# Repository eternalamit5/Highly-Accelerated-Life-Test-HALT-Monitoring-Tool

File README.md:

# Highly Accelerated Life Test (HALT) Profile Monitoring Tool

1. Highly Accelerated Life Testing (HALT) Profile is stress screening methodology where real profiles of data is used to evaluate the reliability of electronics devices, mainly Printed Circuit Boards (PCBs).

2. This project aims at building a tool capable of monitoring HALT Program for identifying defects and weak links in the PCBs.

## Components Used

1. Espressif ESP32 Microcontroller

2. Bosch BMI 160 Inertial Measurement Unit

## Problem
- Lack of proper test screening leads to premature failure of electronics product.

Fig: Capacitor breakage observed during vibration HALT program

- Comparison of raw and calibrated Accelerometer data when Z-axis is facing upward

- Comparison of raw and calibrated Gyroscope data

## Calibration Methodology:

- Three-point calibration of Accelerometer X-axis

- Regression analysis for Gyroscope X-axis data when angular speed= 120 Degree/Sec

## Snapshot of Sensor Dashboard

## Note

1. Since the IoT Stack is very often used in IoT Setups, therefore it is independent, dockerized and can be used standalone for various scenarios. The IoT stack is present in the directory: Highly-Accelerated-Life-Test-HALT-Monitoring-Tool/webClient/IoT Stack

2. Refer to `README.md` in each case directory for additional information.

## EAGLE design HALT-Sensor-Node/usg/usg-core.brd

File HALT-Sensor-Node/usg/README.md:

# Universal Sensor Gateway

## ESP-WROOM-32D Pin Configuration

GPIO | PIN | Functionality | Description | Comment
--|--|--|--|--
0 || Boot Button | General IO |  
1 || UART TX0    | FTDI UART | 
2 || HS2_DATA0   | quad SPI | 
3 || UART RX0    | FTDI UART | 
4 || HS2_DATA1   | quad SPI | 
5 || CS SD Card  | SPI Chip Select | OPTIONAL
6 || FLASH SCK   | Internal Flash ESP32 | 
7 || FLASH DO    | Internal Flash ESP32 | 
8 || FLASH D1    | Internal Flash ESP32 | 
9 || FLASH D2    | Internal Flash ESP32 | U1RXD via Jumper
10 || FLASH D3   | Internal Flash ESP32 | U1TXD via Jumper
11 |  | FLASH CMD | Internal Flash ESP32
12 |  | HS2_DATA2 / TDI | quad SPI | ALSO: JTAG segger
13 |  | HS2_DATA3 / TCK | quad SPI | ALSO: JTAG segger
14 |  | HS2_CLK / TMS | quad SPI | ALSO: JTAG segger
15 |  | HS2_CMD / TDO | quad SPI | ALSO: JTAG segger
16 |  | UART RX2 | CELL UART |
17 |  | UART TX2 | CELL UART |
18 |  | VSPI SCK | mikroBUS SPI |
19 |  | VSPI MISO / Q | mikroBUS SPI |
20 |  |  |  | N/A
21 |  | CS mikroBUS | SPI Chip Select | OPTIONAL
22 |  | Ext.IO | General IO | OPTIONAL
23 |  | VSPI MOSI / D | mikroBUS SPI |
24 |  |  |  | N/A
25 |  | SARA-R4 PWR | General IO |
26 |  | SARA-R4 RESET | General IO |
27 |  | User LED | General IO | OPTIONAL
28 |  |  |  | N/A
29 |  |  |  | N/A
30 |  |  |  | N/A
31 |  |  |  | N/A
32 |  | I2C SCL | Sensor I2C |
33 |  | I2C SDA | Sensor I2C |
34 |  | Ext.Input | General INPUT | OPTIONAL
35 |  |  | General INPUT |
36 |  |  | General INPUT |
37 |  |  |  | N/A
38 |  |  |  | N/A
39 |  |  | General INPUT |
40 |  |  |  | N/A

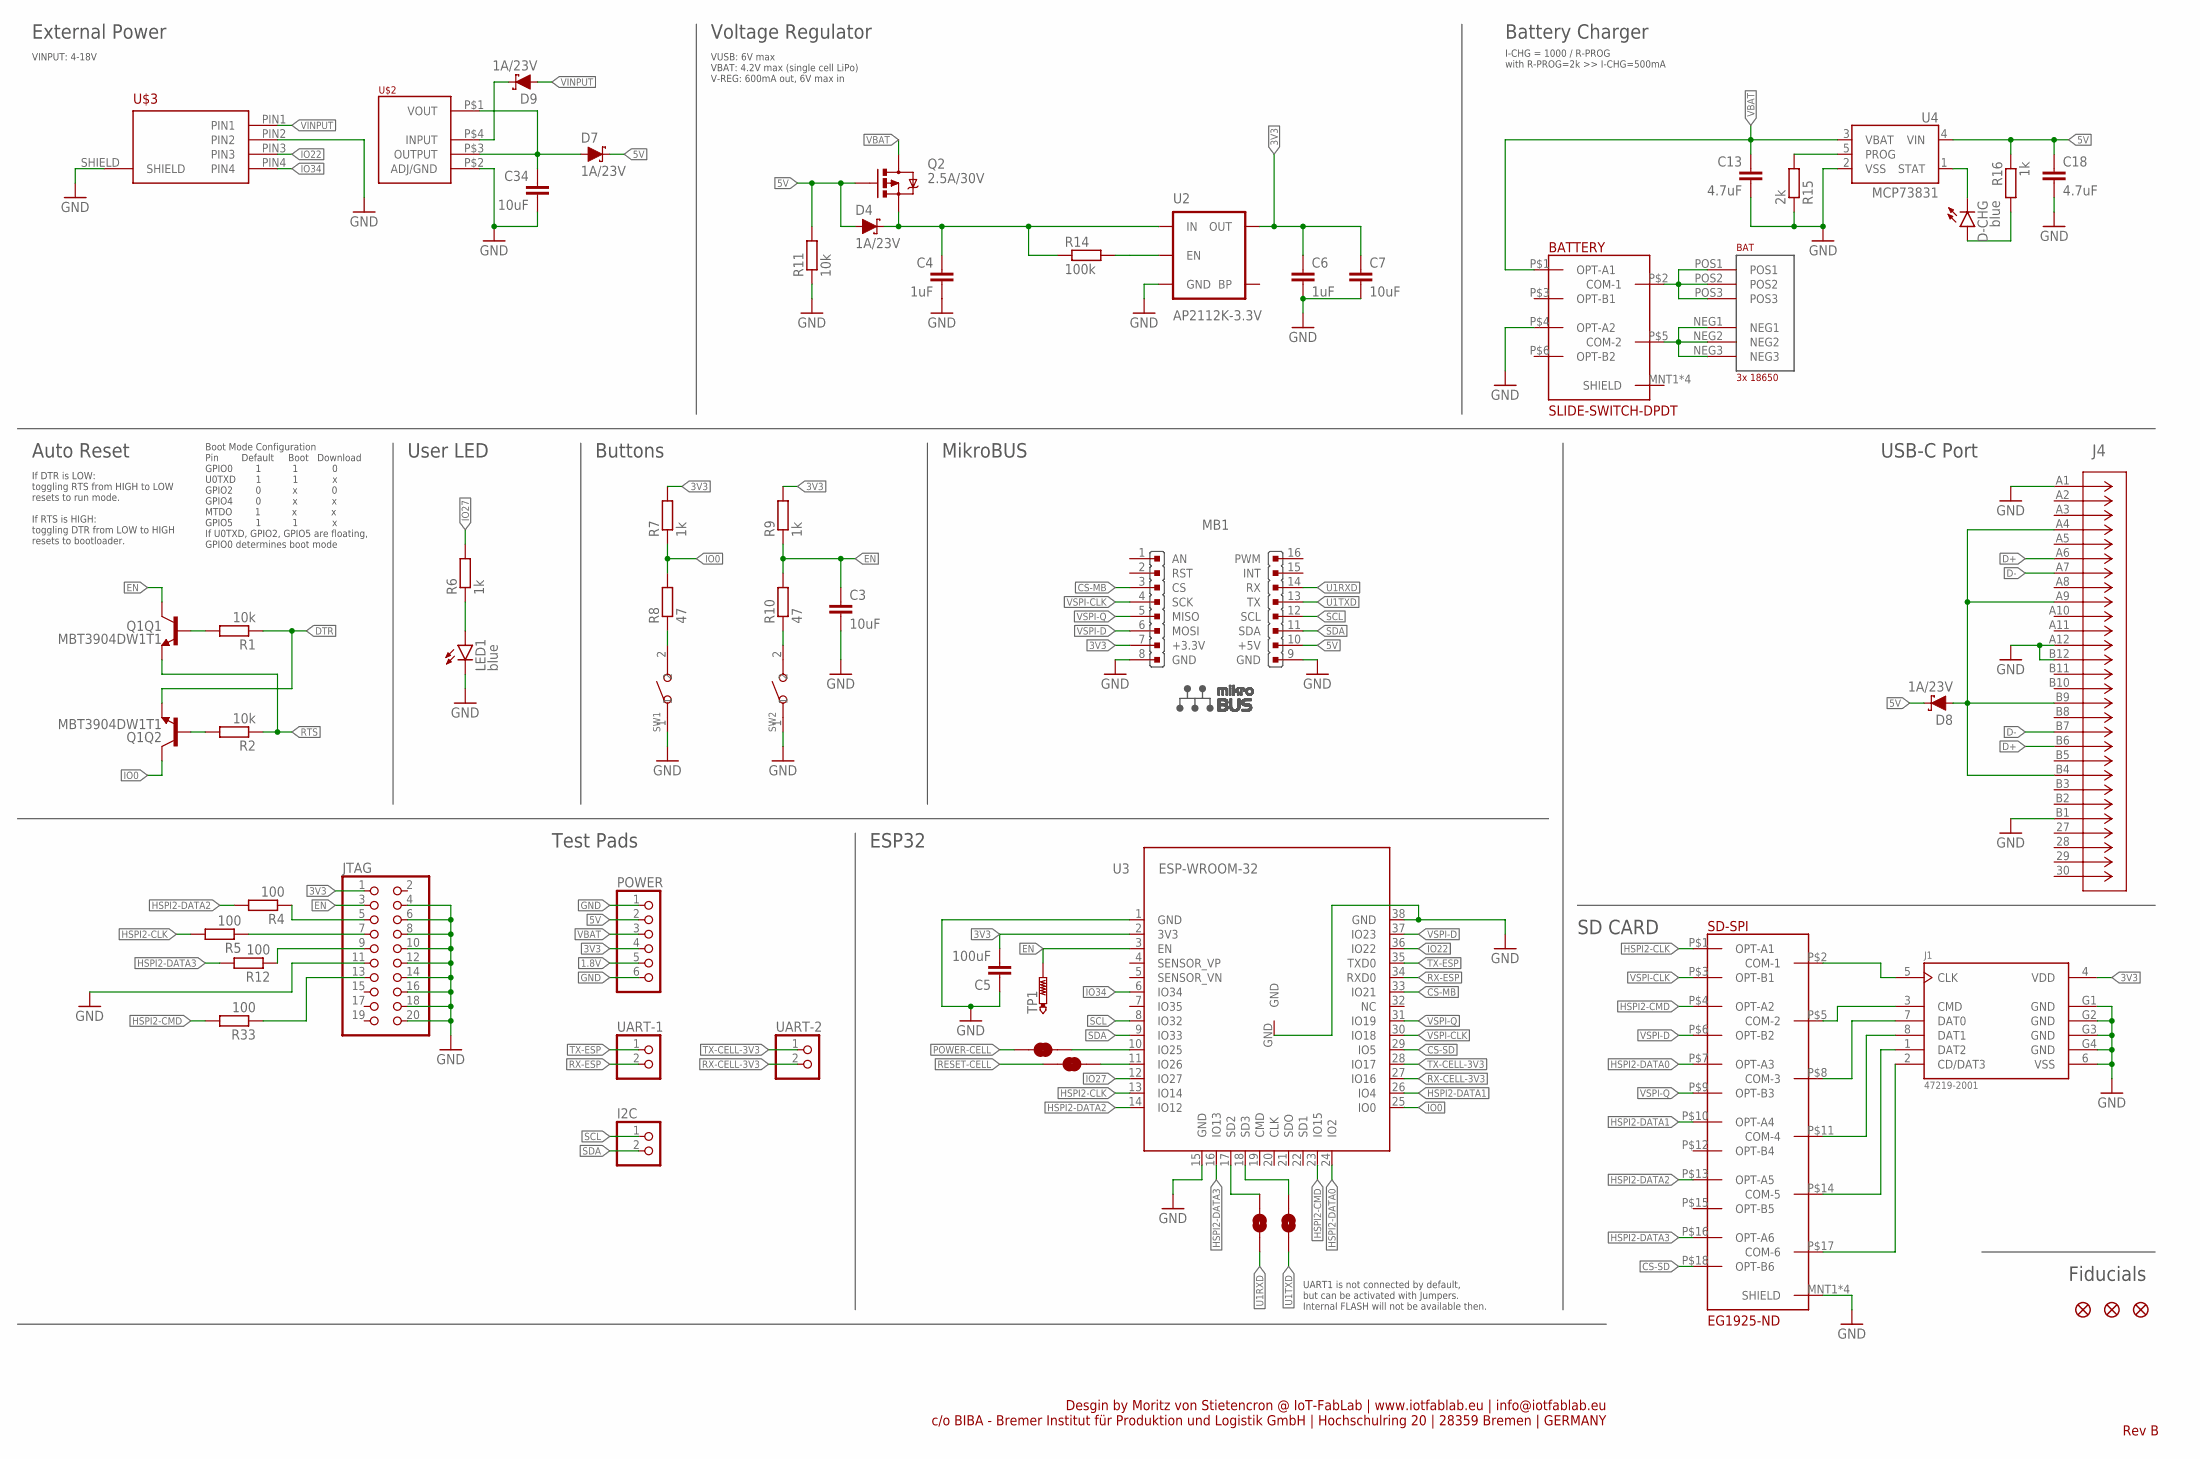
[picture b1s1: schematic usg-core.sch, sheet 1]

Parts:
BAT: 3x 18650; BK-18650-PC6
BATTERY: SLIDE-SWITCH-DPDT
C3, C7, C34: 10uF; C0603
C4, C6: 1uF; C0603
C5: 100uF; C1206
C13, C18: 4.7uF; C0603
D4, D7, D8, D9: 1A/23V; SOD-323
D-CHG: blue; CHIP-LED0603
FD1, FD2, FD3: FIDUCIAL1X2; FIDUCIAL-1X2
I2C: PINHD-1X2; 1X02
J1: 47219-2001; MOLEX_47219-2001
J4: DX07S024WJ3R400; CONN_DX07S024WJ3R400
JP10, JP11: JUMPER-SMT_2_NC_TRACE_SILK; SMT-JUMPER_2_NC_TRACE_SILK
JTAG: PINHD-2X10; 2X10
LED1: blue; CHIP-LED0603
MB1: MIKROBUS
POWER: PINHD-1X6; 1X06
Q1: MBT3904DW1T1; SC70-6
Q2: 2.5A/30V; SOT23-3@1
R1, R2, R11: 10k; R0603
R4, R5, R12, R33: 100; R0603
R6, R7, R9, R16: 1k; R0603
R8, R10: 47; R0603
R14: 100k; R0603
R15: 2k; R0603
SD-SPI: EG1925-ND; SLIDE-SWITCH-6PDT
SJ1, SJ2: JUMPER-SMT_2_NO_SILK; SMT-JUMPER_2_NO_SILK
SW1, SW2: SMD-BUTTON(2P-3.0X2.5X1.2+0.4MM)-B3U-1000P-2P-SMD; SW2-2.6-3.0X2.5X1.2+0.4MM
TP1: PTR1B1,27; B1,27
U2: AP2112K-3.3V; SOT23-5
U3: ESP-WROOM-32
U4: MCP73831; SOT23-5
U$2: LDO-AZ1117I; SOT223
U$3: SACC-CI-M12FSD-4CON-L90
UART-1, UART-2: PINHD-1X2; 1X02

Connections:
1.8V: POWER.5; also elsewhere on the board
3V3: C5.2, C6.1, C7.1, J1.4 (VDD), JTAG.1, MB1.7 (+3.3V), POWER.4, R7.2, R9.2, U2.5 (OUT), U3.2 (3V3); also elsewhere on the board
5V: C18.1, D4.A, D7.C, D8.C, MB1.10 (+5V), POWER.2, Q2.1 (G), R11.2, R16.1, U4.4 (VIN); also elsewhere on the board
BTN1: R10.1, SW2.2
CHG: D-CHG.C, U4.1 (STAT)
CS-MB: MB1.3 (CS), U3.33 (IO21)
CS-SD: SD-SPI.P$18 (OPT-B6), U3.29 (IO5)
D+: J4.A6, J4.B6; also elsewhere on the board
D-: J4.A7, J4.B7; also elsewhere on the board
DTR: Q1.1 (E), R1.1; also elsewhere on the board
EN: C3.1, JTAG.3, Q1.3 (C), R9.1, R10.2, TP1.TP, U3.3 (EN)
EN1: R14.2, U2.3 (EN)
GND: BATTERY.P$4 (OPT-A2), C3.2, C4.2, C5.1, C6.2, C7.2, C13.2, C18.2, C34.2, J1.6 (VSS), J1.G1 (GND), J1.G2 (GND), J1.G3 (GND), J1.G4 (GND), J4.A1, J4.A12, J4.B1, J4.B12, JTAG.4, JTAG.6, JTAG.8, JTAG.10, JTAG.11, JTAG.12, JTAG.14, JTAG.16, JTAG.18, JTAG.20, LED1.C, MB1.8 (GND), MB1.9 (GND), POWER.1, POWER.6, R11.1, R15.1, SD-SPI.MNT1 (SHIELD), SD-SPI.MNT2 (SHIELD), SD-SPI.MNT3 (SHIELD), SD-SPI.MNT4 (SHIELD), SW1.1, SW2.1, U2.2 (GND), U3.1 (GND), U3.15 (GND), U3.38 (GND), U3.GND, U4.2 (VSS), U$2.P$2 (ADJ/GND), U$3.PIN2, U$3.SHIELD; also elsewhere on the board
HSPI2-CLK: R5.2, SD-SPI.P$1 (OPT-A1), U3.13 (IO14)
HSPI2-CMD: R33.2, SD-SPI.P$4 (OPT-A2), U3.23 (IO15)
HSPI2-DATA0: SD-SPI.P$7 (OPT-A3), U3.24 (IO2)
HSPI2-DATA1: SD-SPI.P$10 (OPT-A4), U3.26 (IO4)
HSPI2-DATA2: R4.2, SD-SPI.P$13 (OPT-A5), U3.14 (IO12)
HSPI2-DATA3: R12.2, SD-SPI.P$16 (OPT-A6), U3.16 (IO13)
IO0: Q1.6 (C), R7.1, R8.2, U3.25 (IO0)
IO22: U3.36 (IO22), U$3.PIN3
IO27: R6.2, U3.12 (IO27)
IO34: U3.6 (IO34), U$3.PIN4
unnamed: D9.C, U$2.P$4 (INPUT)
unnamed: D-CHG.A, R16.2
unnamed: R15.2, U4.5 (PROG)
unnamed: Q1.5 (B), R1.2
unnamed: LED1.A, R6.1
unnamed: R8.1, SW1.2
unnamed: Q1.2 (B), R2.2
unnamed: D8.A, J4.A4, J4.A9, J4.B4, J4.B9
unnamed: JP10.2, U3.10 (IO25)
unnamed: JP11.2, U3.11 (IO26)
unnamed: SJ1.2, U3.17 (SD2)
unnamed: SJ2.2, U3.18 (SD3)
unnamed: J1.5 (CLK), SD-SPI.P$2 (COM-1)
unnamed: J1.3 (CMD), SD-SPI.P$5 (COM-2)
unnamed: J1.2 (CD/DAT3), SD-SPI.P$17 (COM-6)
unnamed: J1.1 (DAT2), SD-SPI.P$14 (COM-5)
unnamed: J1.8 (DAT1), SD-SPI.P$11 (COM-4)
unnamed: J1.7 (DAT0), SD-SPI.P$8 (COM-3)
unnamed: JTAG.5, R4.1
unnamed: JTAG.7, R5.1
unnamed: JTAG.9, R12.1
unnamed: JTAG.13, R33.1
unnamed: BAT.POS1, BAT.POS2, BAT.POS3, BATTERY.P$2 (COM-1)
unnamed: BAT.NEG1, BAT.NEG2, BAT.NEG3, BATTERY.P$5 (COM-2)
POWER-CELL: JP10.1; also elsewhere on the board
RESET-CELL: JP11.1; also elsewhere on the board
RTS: Q1.4 (E), R2.1; also elsewhere on the board
RX-CELL-3V3: U3.27 (IO16), UART-2.2; also elsewhere on the board
RX-ESP: U3.34 (RXD0), UART-1.2; also elsewhere on the board
SCL: I2C.1, MB1.12 (SCL), U3.8 (IO32); also elsewhere on the board
SDA: I2C.2, MB1.11 (SDA), U3.9 (IO33); also elsewhere on the board
TX-CELL-3V3: U3.28 (IO17), UART-2.1; also elsewhere on the board
TX-ESP: U3.35 (TXD0), UART-1.1; also elsewhere on the board
U1RXD: MB1.14 (RX), SJ1.1
U1TXD: MB1.13 (TX), SJ2.1
VBAT: BATTERY.P$1 (OPT-A1), C13.1, POWER.3, Q2.3 (D), U4.3 (VBAT)
VIN: C4.1, D4.C, Q2.2 (S), R14.1, U2.1 (IN)
VINPUT: D9.A, U$3.PIN1
VOUT: C34.1, D7.A, U$2.P$1 (VOUT), U$2.P$3 (OUTPUT)
VSPI-CLK: MB1.4 (SCK), SD-SPI.P$3 (OPT-B1), U3.30 (IO18)
VSPI-D: MB1.6 (MOSI), SD-SPI.P$6 (OPT-B2), U3.37 (IO23)
VSPI-Q: MB1.5 (MISO), SD-SPI.P$9 (OPT-B3), U3.31 (IO19)

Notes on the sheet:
Voltage Regulator
Battery Charger
Auto Reset
User LED
USB-C Port
ESP32
Buttons
Fiducials
Desgin by Moritz von Stietencron @ IoT-FabLab | www.iotfablab.eu | info@iotfablab.eu c/o BIBA - Bremer Institut für Produktion und Logistik GmbH | Hochschulring 20 | 28359 Bremen | GERMANY
Rev B
Test Pads
I-CHG = 1000 / R-PROG with R-PROG=2k >> I-CHG=500mA
VUSB: 6V max VBAT: 4.2V max (single cell LiPo) V-REG: 600mA out, 6V max in
If DTR is LOW: toggling RTS from HIGH to LOW resets to run mode. If RTS is HIGH: toggling DTR from LOW to HIGH resets to bootloader.
Boot Mode Configuration Pin Default Boot Download GPIO0 1 1 0 U0TXD 1 1 x GPIO2 0 x 0 GPIO4 0 x x MTDO 1 x x GPIO5 1 1 x If U0TXD, GPIO2, GPIO5 are floating, GPIO0 determines boot mode
MikroBUS
SD CARD
UART1 is not connected by default, but can be activated with Jumpers. Internal FLASH will not be available then.
External Power
VINPUT: 4-18V

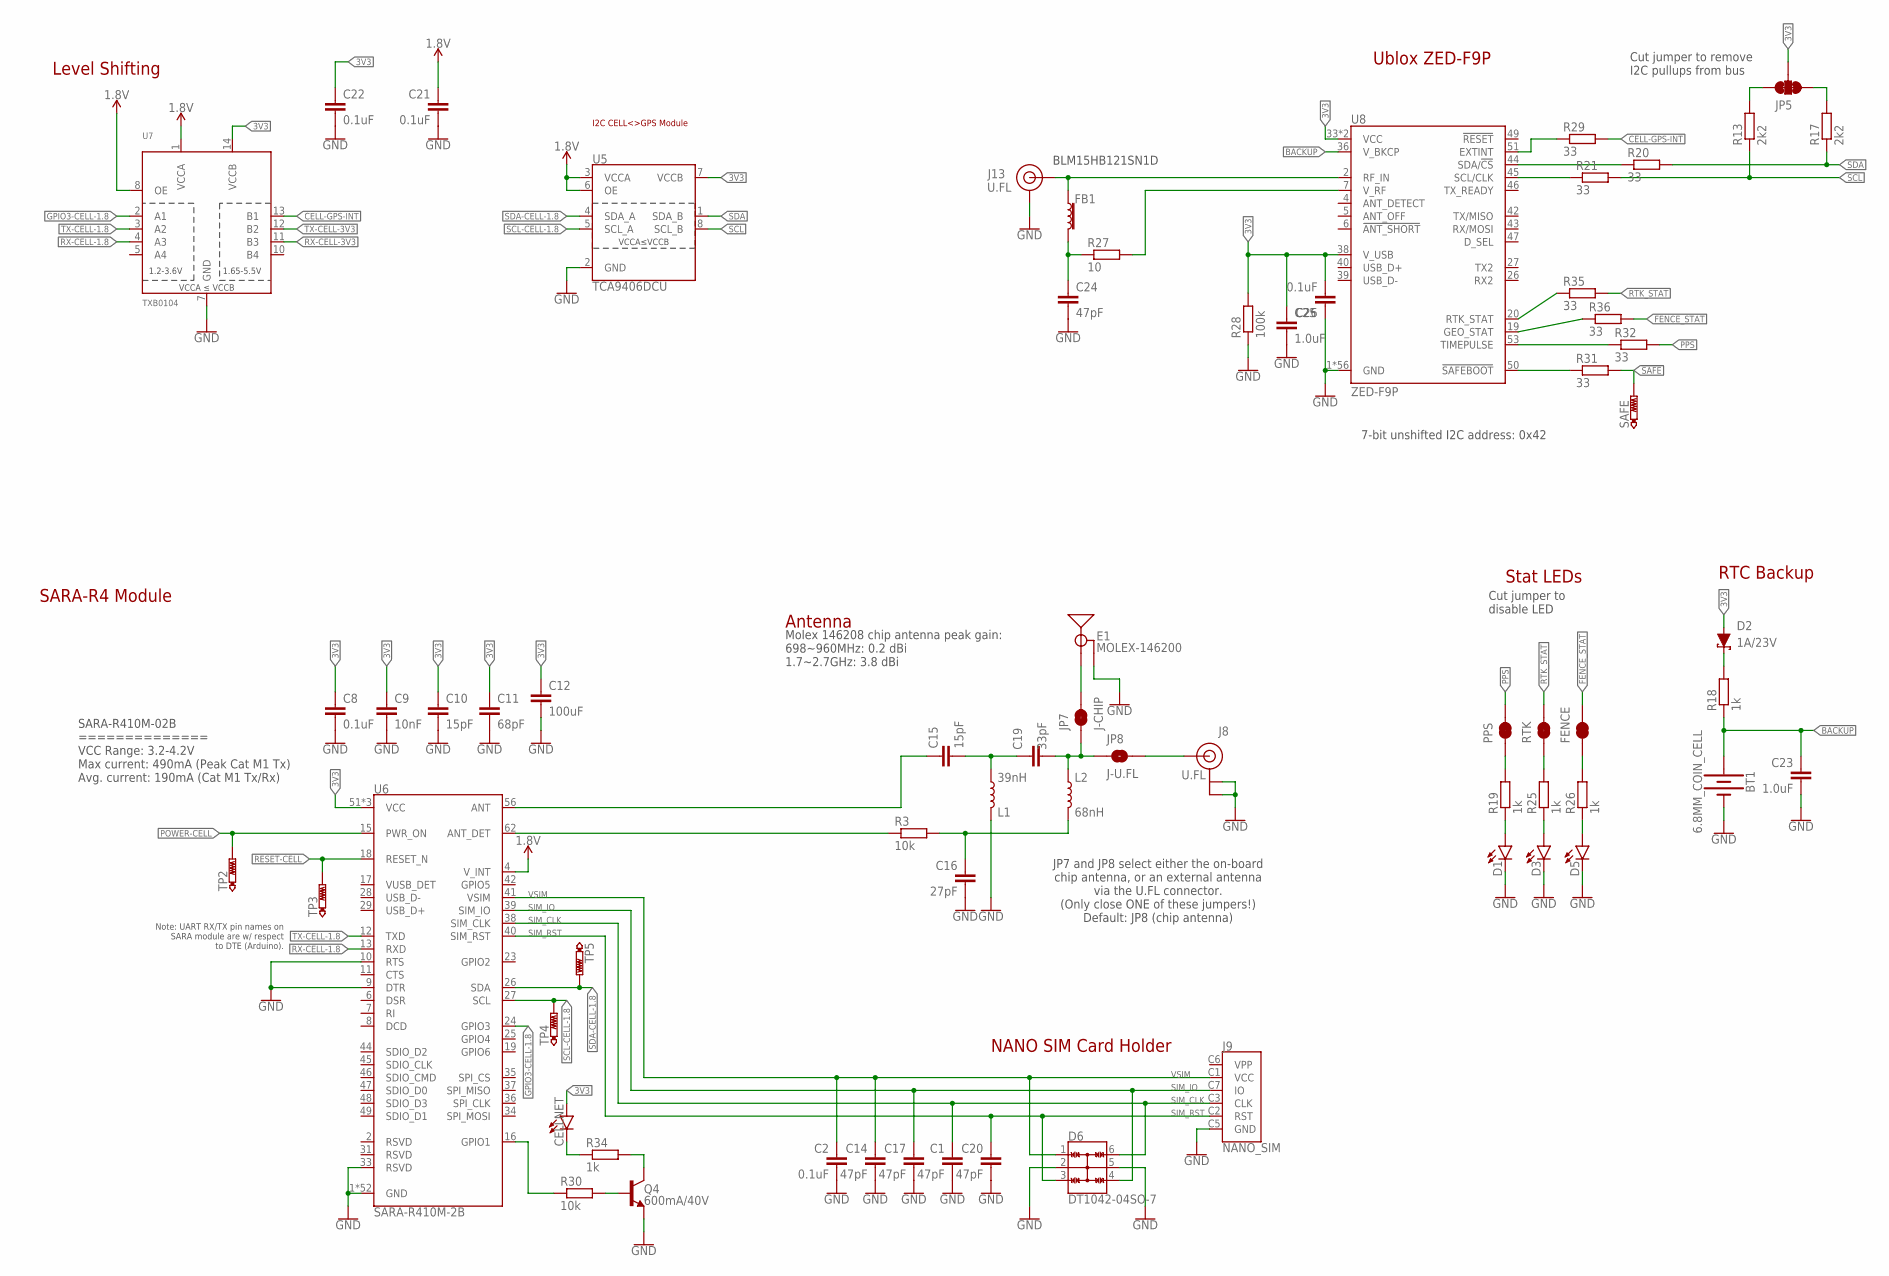
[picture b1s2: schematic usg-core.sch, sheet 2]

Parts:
BT1: 6.8MM_COIN_CELL; BATTCON-6.8MM
C1, C14, C17, C20, C24: 47pF; C0603
C2, C8, C21, C22, C26: 0.1uF; C0603
C9: 10nF; C0603
C10, C15: 15pF; C0603
C11: 68pF; C0603
C12: 100uF; C1206
C16: 27pF; C0603
C19: 33pF; C0603
C23, C25: 1.0uF; C0603
CELLNET: blue; CHIP-LED0603
D1, D3, D5: blue; CHIP-LED0603
D2: 1A/23V; SOD-323
D6: DT1042-04SO-7; SOT23-6L
E1: MOLEX-146200; MOLEX_146200
FB1: FERRITE_BEAD-120_OHM-0402; 0402
FENCE: JUMPER-SMT_2_NC_TRACE_SILK; SMT-JUMPER_2_NC_TRACE_SILK
J8, J13: U.FL
J9: NANO_SIM; NANO_SIM_WURTH_693043020611
JP5: JUMPER-SMT_3_2-NC_TRACE_SILK; SMT-JUMPER_3_2-NC_TRACE_SILK
JP7: J-CHIP; SMT-JUMPER_2_NC_TRACE_NO-SILK
JP8: J-U.FL; SMT-JUMPER_2_NO_NO-SILK
L1: 39nH; 0603
L2: 68nH; 0603
PPS: JUMPER-SMT_2_NC_TRACE_SILK; SMT-JUMPER_2_NC_TRACE_SILK
Q4: 600mA/40V; SOT23-3
R3, R30: 10k; R0603
R13, R17: 2k2; R0603
R18, R19, R25, R26, R34: 1k; R0603
R20, R21, R29, R31, R32, R35, R36: 33; R0603
R27: 10; R0603
R28: 100k; R0603
RTK: JUMPER-SMT_2_NC_TRACE_SILK; SMT-JUMPER_2_NC_TRACE_SILK
SAFE: PTR1B1,27; B1,27
TP2, TP3, TP4, TP5: PTR1B1,27; B1,27
U5: TCA9406DCU; VSSOP-8
U6: SARA-R410M-2B; SARA-LGA
U7: TXB0104; TSSOP14
U8: ZED-F9P

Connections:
1.8V: C21.1, U5.3 (VCCA), U5.6 (OE), U6.4 (V_INT), U7.1 (VCCA), U7.8 (OE); also elsewhere on the board
3V3: C8.1, C9.1, C10.1, C11.1, C12.1, C22.1, C25.1, C26.2, CELLNET.A, D2.A, JP5.2, R28.2, U5.7 (VCCB), U6.51 (VCC), U6.52 (VCC), U6.53 (VCC), U7.14 (VCCB), U8.33 (VCC), U8.34 (VCC), U8.38 (V_USB); also elsewhere on the board
!SAFE: R31.2, SAFE.TP
ANT: C15.1, U6.56 (ANT)
ANT_DET: R3.1, U6.62 (ANT_DET)
ANT_VCC: C24.1, FB1.2, R27.1
BACKUP: BT1.+, C23.1, R18.1, U8.36 (V_BKCP)
CELL-GPS-INT: R29.2, U7.13 (B1)
FENCE_STAT: FENCE.2, R36.2
GND: BT1.-, C1.2, C2.2, C8.2, C9.2, C10.2, C11.2, C12.2, C14.2, C16.2, C17.2, C20.2, C21.2, C22.2, C23.2, C24.2, C25.2, C26.1, D1.C, D3.C, D5.C, D6.2, D6.5, E1.GND, J8.1 (GND), J8.2 (GND), J9.C5 (GND), J13.1 (GND), J13.2 (GND), L1.1, Q4.2 (E), R28.1, U5.2 (GND), U6.1 (GND), U6.3 (GND), U6.5 (GND), U6.9 (DTR), U6.10 (RTS), U6.14 (GND), U6.20 (GND), U6.21 (GND), U6.22 (GND), U6.30 (GND), U6.32 (GND), U6.33 (RSVD), U6.43 (GND), U6.50 (GND), U6.54 (GND), U6.55 (GND), U6.57 (GND), U6.58 (GND), U6.59 (GND), U6.60 (GND), U6.61 (GND), U6.63 (GND), U6.64 (GND), U6.65 (GND), U6.66 (GND), U6.67 (GND), U6.68 (GND), U6.69 (GND), U6.70 (GND), U6.71 (GND), U6.72 (GND), U6.73 (GND), U6.74 (GND), U6.75 (GND), U6.76 (GND), U6.77 (GND), U6.78 (GND), U6.79 (GND), U6.80 (GND), U6.81 (GND), U6.82 (GND), U6.83 (GND), U6.84 (GND), U6.85 (GND), U6.86 (GND), U6.87 (GND), U6.88 (GND), U6.89 (GND), U6.90 (GND), U6.91 (GND), U6.92 (GND), U6.93 (GND), U6.94 (GND), U6.95 (GND), U6.96 (GND), U7.7 (GND), U8.1 (GND), U8.3 (GND), U8.12 (GND), U8.14 (GND), U8.32 (GND), U8.37 (GND), U8.41 (GND), U8.48 (GND), U8.55 (GND), U8.56 (GND), U8.57 (GND), U8.58 (GND), U8.59 (GND), U8.60 (GND), U8.61 (GND), U8.62 (GND), U8.63 (GND), U8.64 (GND), U8.65 (GND), U8.66 (GND), U8.67 (GND), U8.68 (GND), U8.69 (GND), U8.70 (GND), U8.71 (GND), U8.72 (GND), U8.73 (GND), U8.74 (GND), U8.75 (GND), U8.76 (GND), U8.77 (GND), U8.78 (GND), U8.79 (GND), U8.80 (GND), U8.81 (GND), U8.82 (GND), U8.83 (GND), U8.84 (GND), U8.85 (GND), U8.86 (GND), U8.87 (GND), U8.88 (GND), U8.89 (GND), U8.90 (GND), U8.91 (GND), U8.92 (GND), U8.93 (GND), U8.94 (GND), U8.95 (GND), U8.96 (GND), U8.97 (GND), U8.98 (GND), U8.99 (GND), U8.100 (GND), U8.101 (GND), U8.102 (GND); also elsewhere on the board
GPIO3-CELL-1.8: U6.24 (GPIO3), U7.2 (A1)
GPS_ANT1: FB1.1, J13.FEED (SIGNAL), U8.2 (RF_IN)
unnamed: C16.1, L2.2, R3.2
unnamed: C19.2, JP7.1, JP8.1, L2.1
unnamed: C15.2, C19.1, L1.2
unnamed: J8.FEED (SIGNAL), JP8.2
unnamed: E1.FEED (SIGNAL), JP7.2
unnamed: JP5.1, R17.2
unnamed: JP5.3, R13.2
unnamed: D1.A, R19.1
unnamed: PPS.1, R19.2
unnamed: D2.C, R18.2
unnamed: D3.A, R25.1
unnamed: R25.2, RTK.1
unnamed: D5.A, R26.1
unnamed: FENCE.1, R26.2
unnamed: R27.2, U8.7 (V_RF)
unnamed: R32.1, U8.53 (TIMEPULSE)
unnamed: R31.1, U8.50 (!SAFEBOOT!)
unnamed: R35.1, U8.20 (RTK_STAT)
unnamed: R36.1, U8.19 (GEO_STAT)
unnamed: R29.1, U8.51 (EXTINT)
unnamed: Q4.3 (C), R34.2
unnamed: Q4.1 (B), R30.2
unnamed: R30.1, U6.16 (GPIO1)
unnamed: CELLNET.C, R34.1
POWER-CELL: TP2.TP, U6.15 (PWR_ON); also elsewhere on the board
PPS: PPS.2, R32.2
RESET-CELL: TP3.TP, U6.18 (RESET_N); also elsewhere on the board
RTK_STAT: R35.2, RTK.2
RX-CELL-1.8: U6.13 (RXD), U7.4 (A3)
RX-CELL-3V3: U7.11 (B3); also elsewhere on the board
SCL: R13.1, R21.2, U5.8 (SCL_B); also elsewhere on the board
SCL-CELL-1.8: TP4.TP, U5.5 (SCL_A), U6.27 (SCL)
SCL_LV: R21.1, U8.45 (SCL/CLK)
SDA: R17.1, R20.2, U5.1 (SDA_B); also elsewhere on the board
SDA-CELL-1.8: TP5.TP, U5.4 (SDA_A), U6.26 (SDA)
SDA_LV: R20.1, U8.44 (SDA/!CS!)
SIM_CLK: C1.1, D6.6, J9.C3 (CLK), U6.38 (SIM_CLK)
SIM_IO: C17.1, D6.4, J9.C7 (IO), U6.39 (SIM_IO)
SIM_RST: C20.1, D6.3, J9.C2 (RST), U6.40 (SIM_RST)
TX-CELL-1.8: U6.12 (TXD), U7.3 (A2)
TX-CELL-3V3: U7.12 (B2); also elsewhere on the board
VSIM: C2.1, C14.1, D6.1, J9.C1 (VCC), U6.41 (VSIM)

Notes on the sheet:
Antenna
SARA-R4 Module
NANO SIM Card Holder
JP7 and JP8 select either the on-board chip antenna, or an external antenna via the U.FL connector. (Only close ONE of these jumpers!) Default: JP8 (chip antenna)
Note: UART RX/TX pin names on SARA module are w/ respect to DTE (Arduino).
Molex 146208 chip antenna peak gain: 698~960MHz: 0.2 dBi 1.7~2.7GHz: 3.8 dBi
SARA-R410M-02B ============== VCC Range: 3.2-4.2V Max current: 490mA (Peak Cat M1 Tx) Avg. current: 190mA (Cat M1 Tx/Rx)
Level Shifting
I2C CELL<>GPS Module
7-bit unshifted I2C address: 0x42
Ublox ZED-F9P
Cut jumper to remove I2C pullups from bus
BLM15HB121SN1D
RTC Backup
Stat LEDs
Cut jumper to disable LED

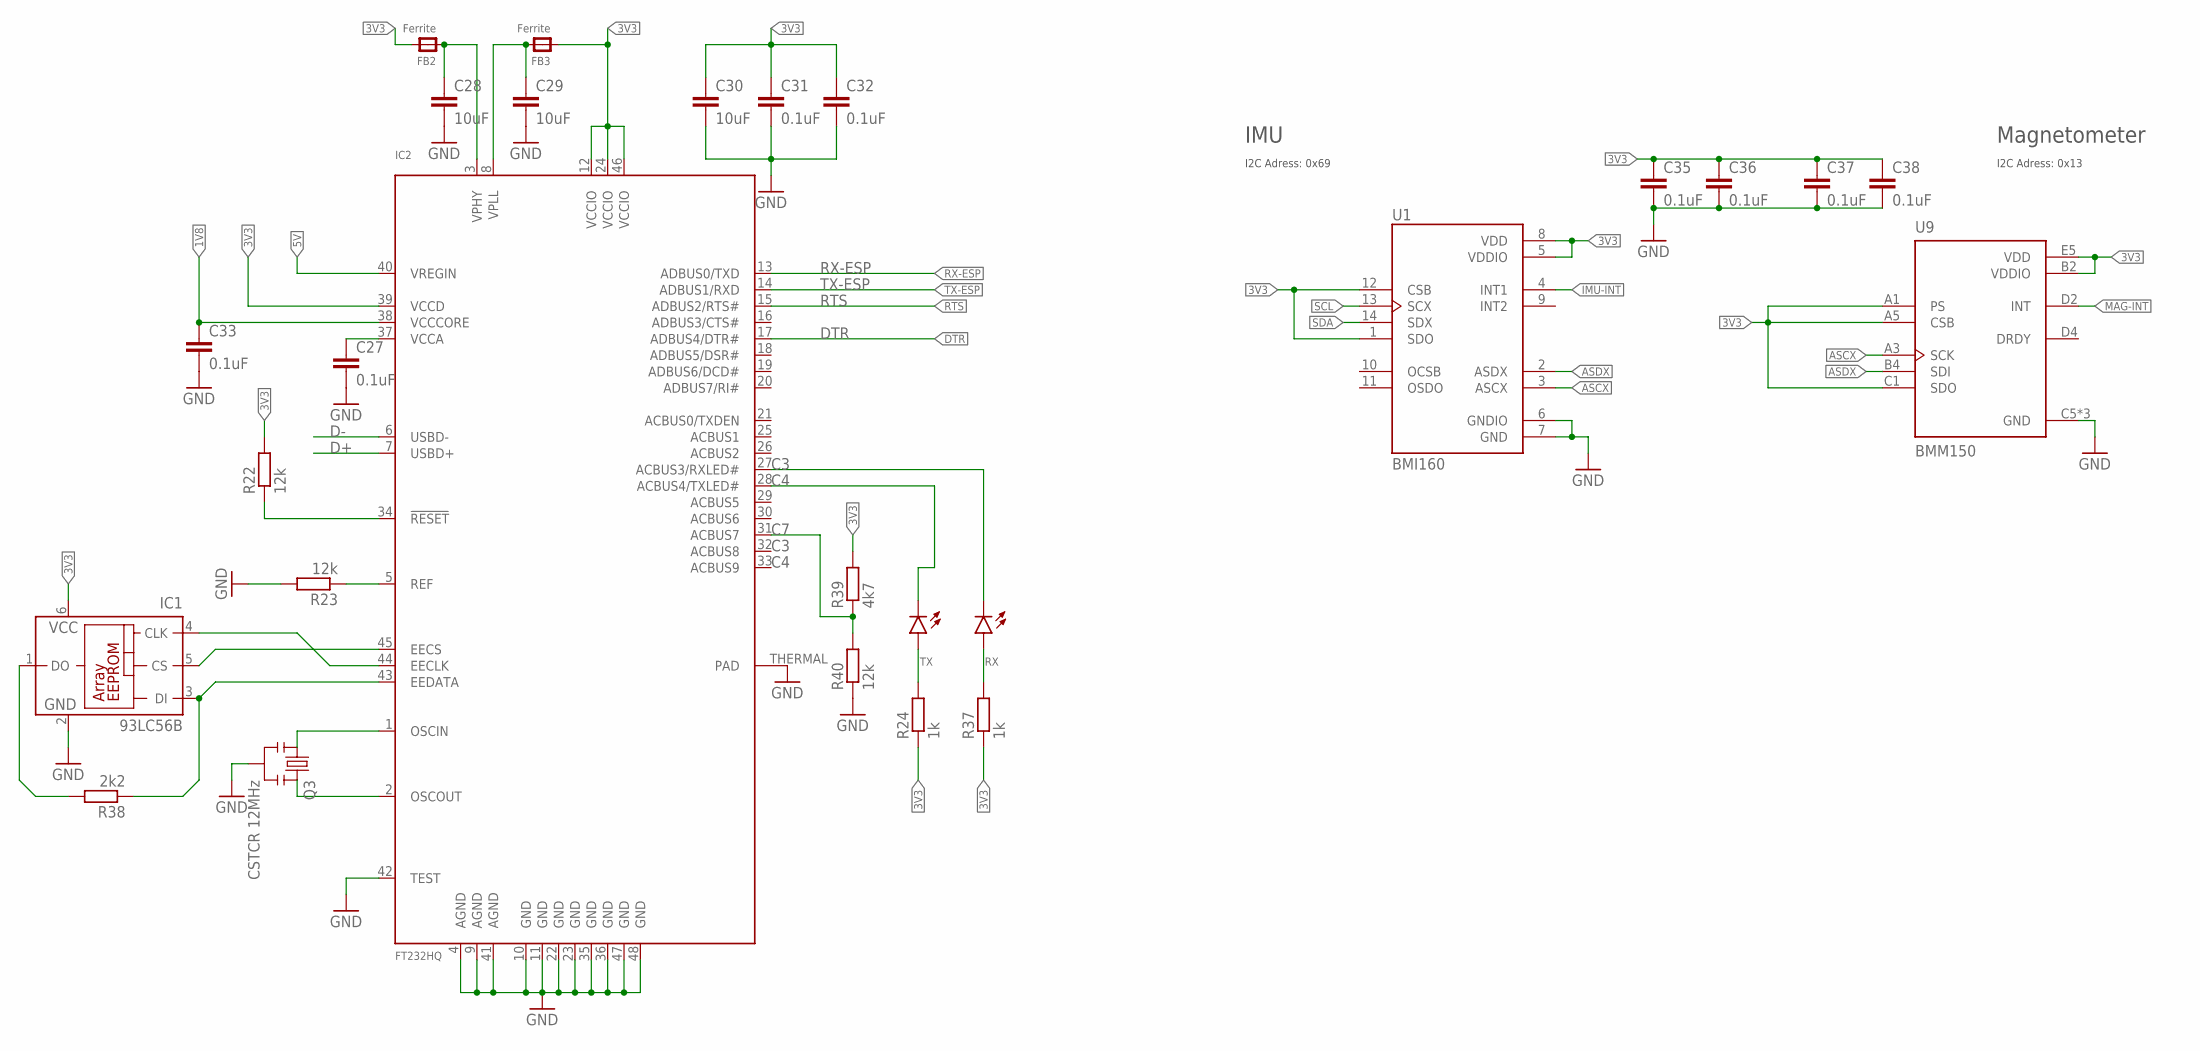
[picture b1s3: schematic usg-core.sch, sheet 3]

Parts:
C27, C31, C32, C33, C35, C36, C37, C38: 0.1uF; C0603
C28, C29, C30: 10uF; C0603
FB2, FB3: Ferrite; _0805
IC1: 93LC56B; SOT23-6
IC2: FT232HQ; QFN48_8MM
Q3: CSTCR 12MHz; RESONATOR-SMD
R22, R23, R40: 12k; R0603
R24, R37: 1k; R0603
R38: 2k2; R0603
R39: 4k7; R0603
RX: blue; CHIP-LED0603
TX: blue; CHIP-LED0603
U1: BMI160; PQFN50P300X250X88-14N
U9: BMM150; XDCR_BMM150

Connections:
1V8: C33.1, IC2.38 (VCCCORE)
3V3: C30.1, C31.1, C32.1, C35.1, C36.1, C37.1, C38.1, FB2.2, FB3.1, IC1.6 (VCC), IC2.12 (VCCIO), IC2.24 (VCCIO), IC2.39 (VCCD), IC2.46 (VCCIO), R22.2, R24.1, R37.1, R39.2, U1.1 (SDO), U1.5 (VDDIO), U1.8 (VDD), U1.12 (CSB), U9.A1 (PS), U9.A5 (CSB), U9.B2 (VDDIO), U9.C1 (SDO), U9.E5 (VDD); also elsewhere on the board
5V: IC2.40 (VREGIN); also elsewhere on the board
ASCX: U1.3 (ASCX), U9.A3 (SCK)
ASDX: U1.2 (ASDX), U9.B4 (SDI)
C3: IC2.27 (ACBUS3/RXLED#), RX.C
C4: IC2.28 (ACBUS4/TXLED#), TX.C
C7: IC2.31 (ACBUS7), R39.1, R40.2
D+: IC2.7 (USBD+); also elsewhere on the board
D-: IC2.6 (USBD-); also elsewhere on the board
DTR: IC2.17 (ADBUS4/DTR#); also elsewhere on the board
GND: C27.2, C28.2, C29.2, C30.2, C31.2, C32.2, C33.2, C35.2, C36.2, C37.2, C38.2, IC1.2 (GND), IC2.4 (AGND), IC2.9 (AGND), IC2.10 (GND), IC2.11 (GND), IC2.22 (GND), IC2.23 (GND), IC2.35 (GND), IC2.36 (GND), IC2.41 (AGND), IC2.42 (TEST), IC2.47 (GND), IC2.48 (GND), IC2.THERMAL (PAD), Q3.2, R23.2, R40.1, U1.6 (GNDIO), U1.7 (GND), U9.C5 (GND), U9.E1 (GND), U9.E3 (GND); also elsewhere on the board
IMU-INT: U1.4 (INT1)
MAG-INT: U9.D2 (INT)
unnamed: IC2.1 (OSCIN), Q3.1
unnamed: IC2.2 (OSCOUT), Q3.3
unnamed: IC2.34 (!RESET), R22.1
unnamed: IC2.5 (REF), R23.1
unnamed: R37.2, RX.A
unnamed: R24.2, TX.A
unnamed: IC1.3 (DI), IC2.43 (EEDATA), R38.1
unnamed: IC1.5 (CS), IC2.45 (EECS)
unnamed: IC1.4 (CLK), IC2.44 (EECLK)
unnamed: IC1.1 (DO), R38.2
RTS: IC2.15 (ADBUS2/RTS#); also elsewhere on the board
RX-ESP: IC2.13 (ADBUS0/TXD); also elsewhere on the board
SCL: U1.13 (SCX); also elsewhere on the board
SDA: U1.14 (SDX); also elsewhere on the board
TX-ESP: IC2.14 (ADBUS1/RXD); also elsewhere on the board
VCCA: C27.1, IC2.37 (VCCA)
VPHY: C28.1, FB2.1, IC2.3 (VPHY)
VPLL: C29.1, FB3.2, IC2.8 (VPLL)

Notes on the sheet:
IMU
I2C Adress: 0x69
I2C Adress: 0x13
Magnetometer

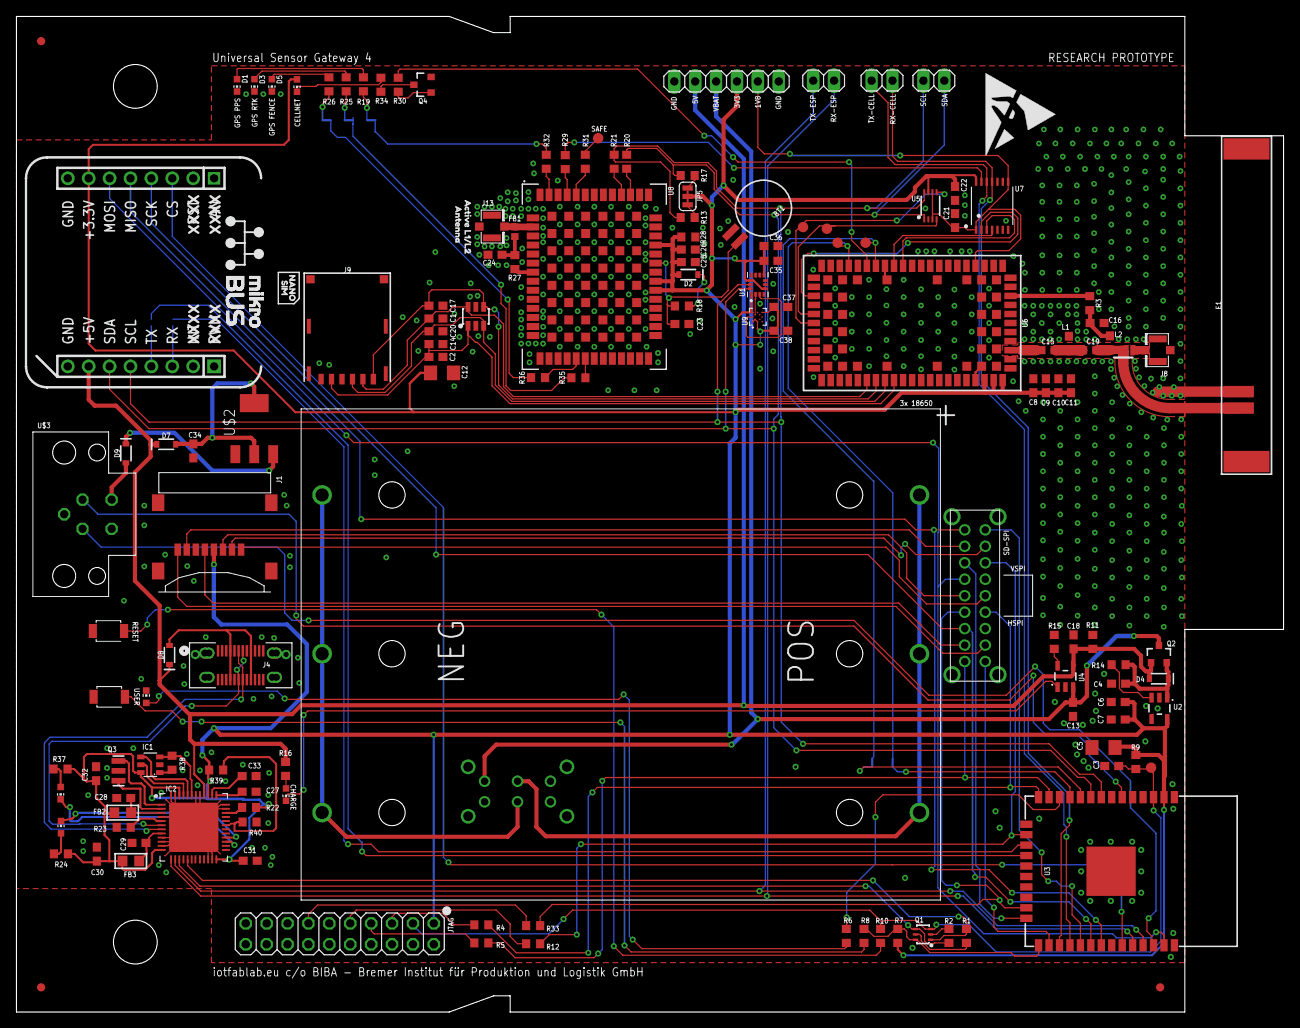
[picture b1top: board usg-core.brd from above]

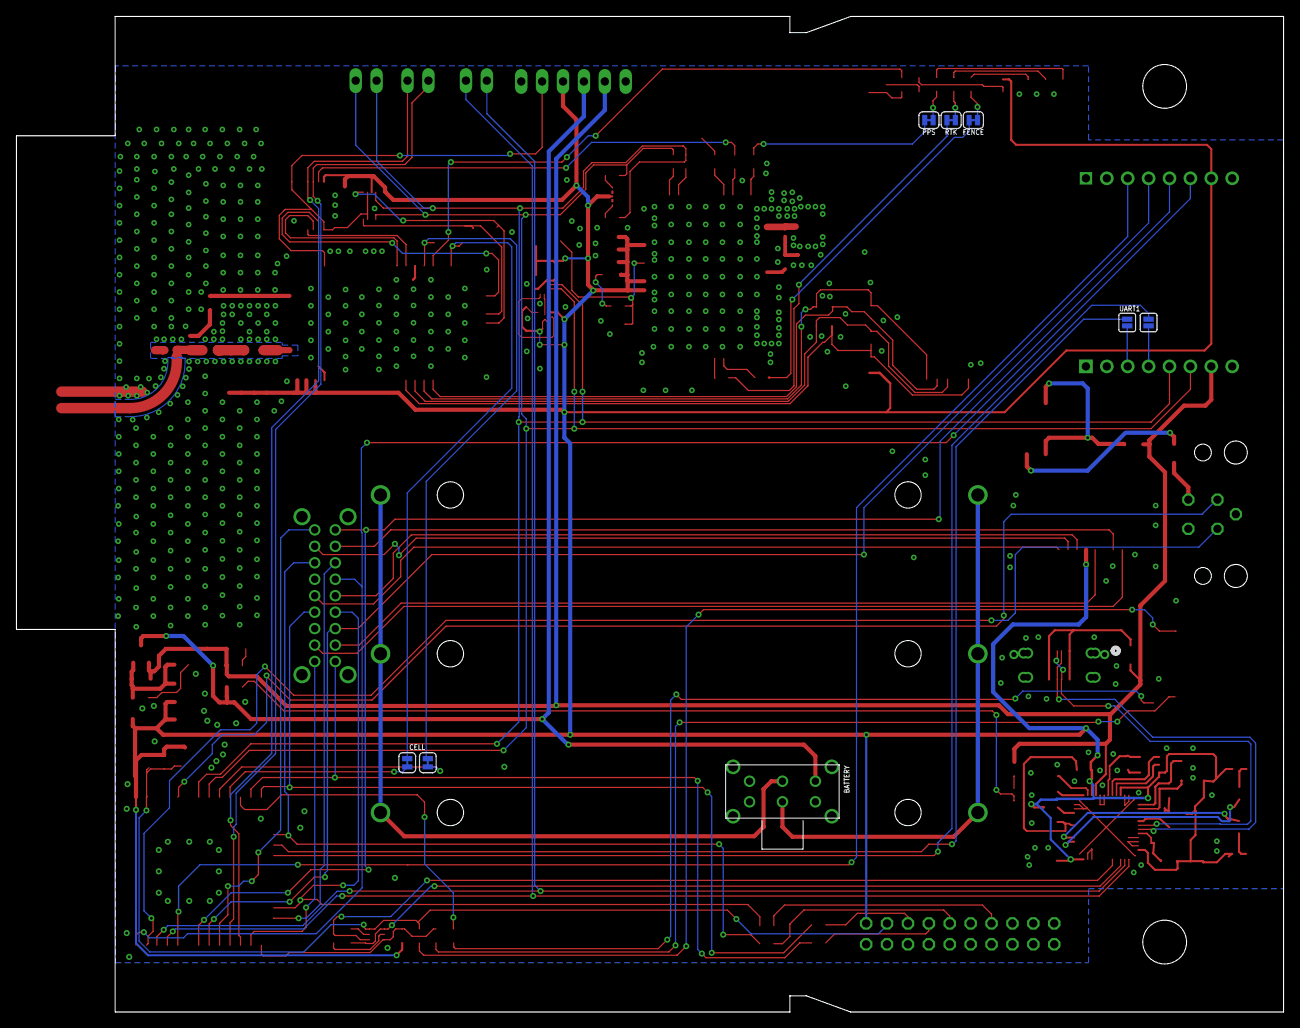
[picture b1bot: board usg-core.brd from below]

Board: 2 copper layers, 154.0 x 121.0 mm, 156 parts (8 on the bottom side), 129 nets.

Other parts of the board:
U$1: ESD_10.00
U$54: NANO50
U$55: SIM51
U$65: ACTIVE_L1#L21
U$71: ANTENNA2

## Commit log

2021-05-02 added the server code base
2021-05-02 added the WebClient code base
2021-05-02 added the HALT IoT stack containing Telegraf + InfluxDB + Grafana + MongoDBwith Mosquitto MQTT broker
2021-05-02 folder rearrangement
2021-05-02 updated the license
2021-05-02 added the sensor node and IMU calibration code base
2021-05-02 added comments in server
2021-05-02 added the sensor node code base
2021-05-02 esp idf
2023-06-20 added the filters and anamoly detection code

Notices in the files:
parts and their libraries:
SparkFun-Aesthetics: Licensing: Creative Commons ShareAlike 4.0 International - https://creativecommons.org/licenses/by-sa/4.0
microbuilder: This work is placed in the public domain, and may be freely used for commercial and non-commercial work with the following conditions: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
